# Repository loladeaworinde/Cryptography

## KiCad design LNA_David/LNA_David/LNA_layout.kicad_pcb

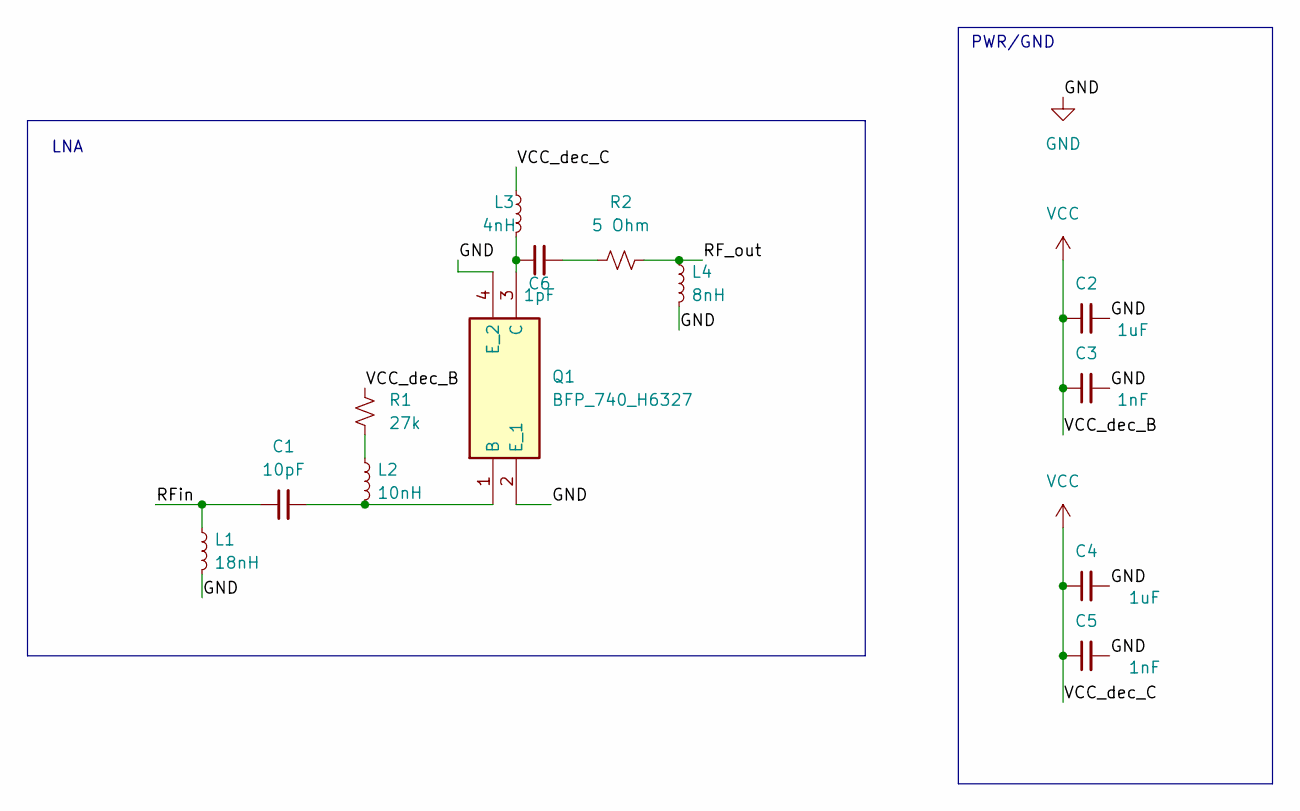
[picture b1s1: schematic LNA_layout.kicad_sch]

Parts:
C1: 10pF; C_0402_1005Metric
C2, C4: 1uF; C_0603_1608Metric
C3, C5: 1nF; C_0603_1608Metric
C6: 1pF; C_0402_1005Metric
L1: 18nH; L_0402_1005Metric
L2: 10nH; L_0402_1005Metric
L3: 4nH; L_0402_1005Metric
L4: 8nH; L_0402_1005Metric
Q1: BFP_740_H6327; BFP740H6327; Mouser Part Number 726-BFP740H6327
R1: 27k; R_0603_1608Metric
R2: 5 Ohm; R_0402_1005Metric

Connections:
/RF_out: L4.1, R2.2
/RFin: C1.1, L1.1
GND: C2.2, C3.2, C4.2, C5.2, L1.2, L4.2, Q1.2 (E_1), Q1.4 (E_2)
unnamed: C6.2, R2.1
unnamed: L2.1, R1.2
unnamed: C1.2, L2.2, Q1.1 (B)
unnamed: C6.1, L3.2, Q1.3 (C)
VCC: C2.1, C3.1, C4.1, C5.1, L3.1, R1.1

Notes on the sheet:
PWR/GND
LNA

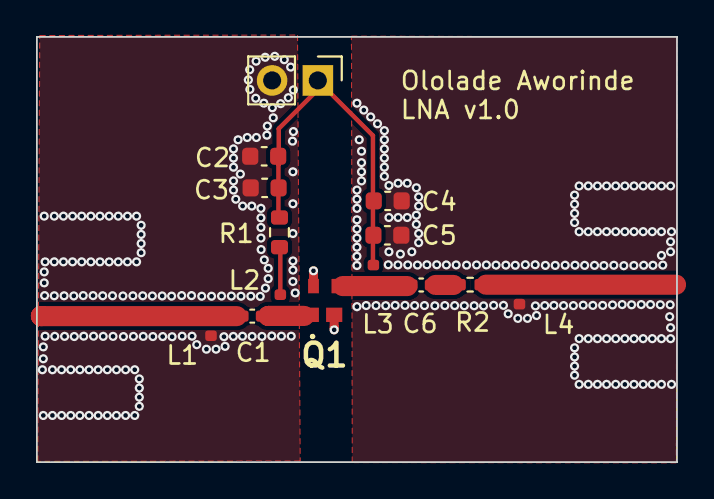
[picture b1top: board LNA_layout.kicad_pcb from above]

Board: 2 copper layers, 35.6 x 23.6 mm, 13 parts (0 on the bottom side), 8 nets.

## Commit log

2024-06-28 remove
